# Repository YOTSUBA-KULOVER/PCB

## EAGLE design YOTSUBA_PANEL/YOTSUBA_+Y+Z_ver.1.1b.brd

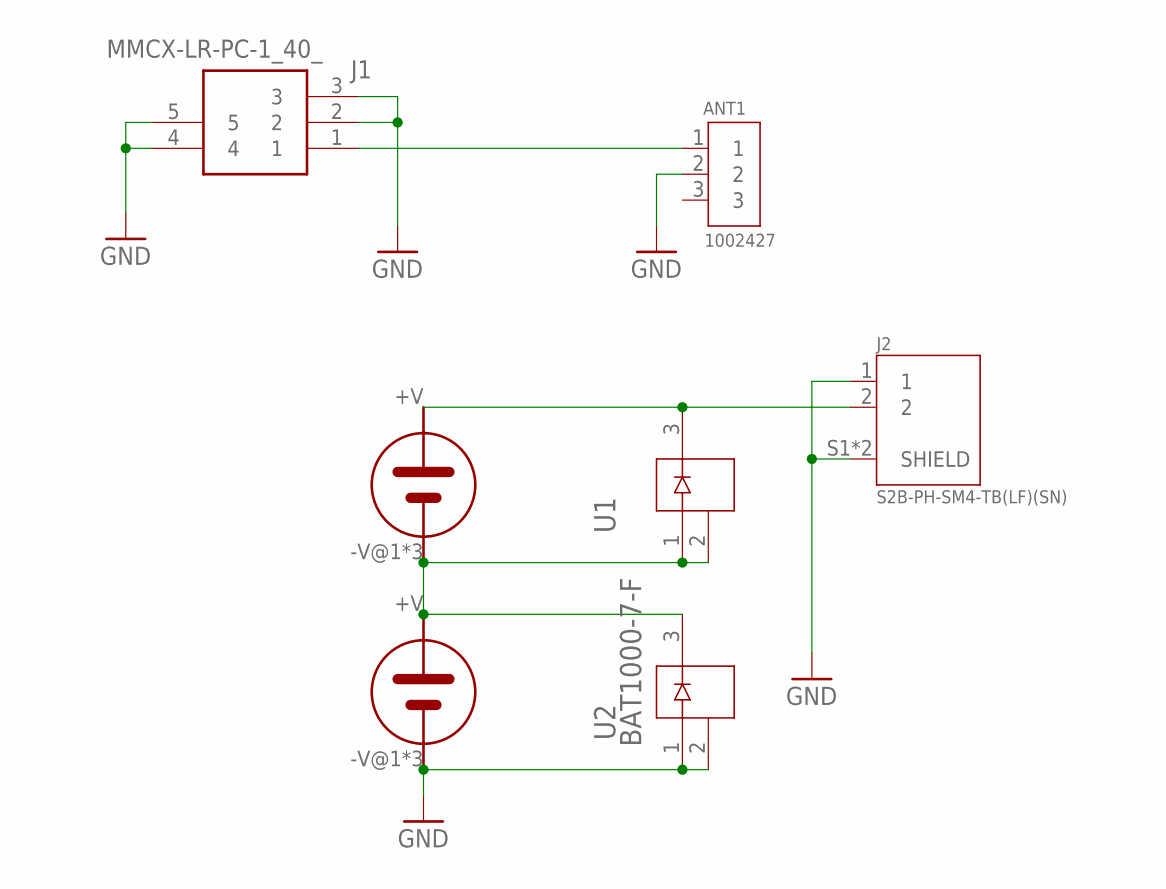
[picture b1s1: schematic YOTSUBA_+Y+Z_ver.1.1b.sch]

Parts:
ANT1: 1002427; ANTENNA_1002427
J1: MMCX-LR-PC-1_40_; MMCXLRPC140
J2: S2B-PH-SM4-TB(LF)(SN); JST_S2B-PH-SM4-TB(LF)(SN)
U1, U2: BAT1000-7-F; SOT23_BAT_DIO
U$2, U$3: 3G30A; SOLAR_3G30A

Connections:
GND: ANT1.2, J1.2, J1.3, J1.4, J1.5, J2.1, J2.S1 (SHIELD), J2.S2 (SHIELD), U2.1, U2.2, U$3.-V@1 (-V), U$3.-V@2 (-V), U$3.-V@3 (-V)
unnamed: U1.1, U1.2, U2.3, U$2.-V@1 (-V), U$2.-V@2 (-V), U$2.-V@3 (-V), U$3.+V
unnamed: J2.2, U1.3, U$2.+V
RF2: ANT1.1, J1.1

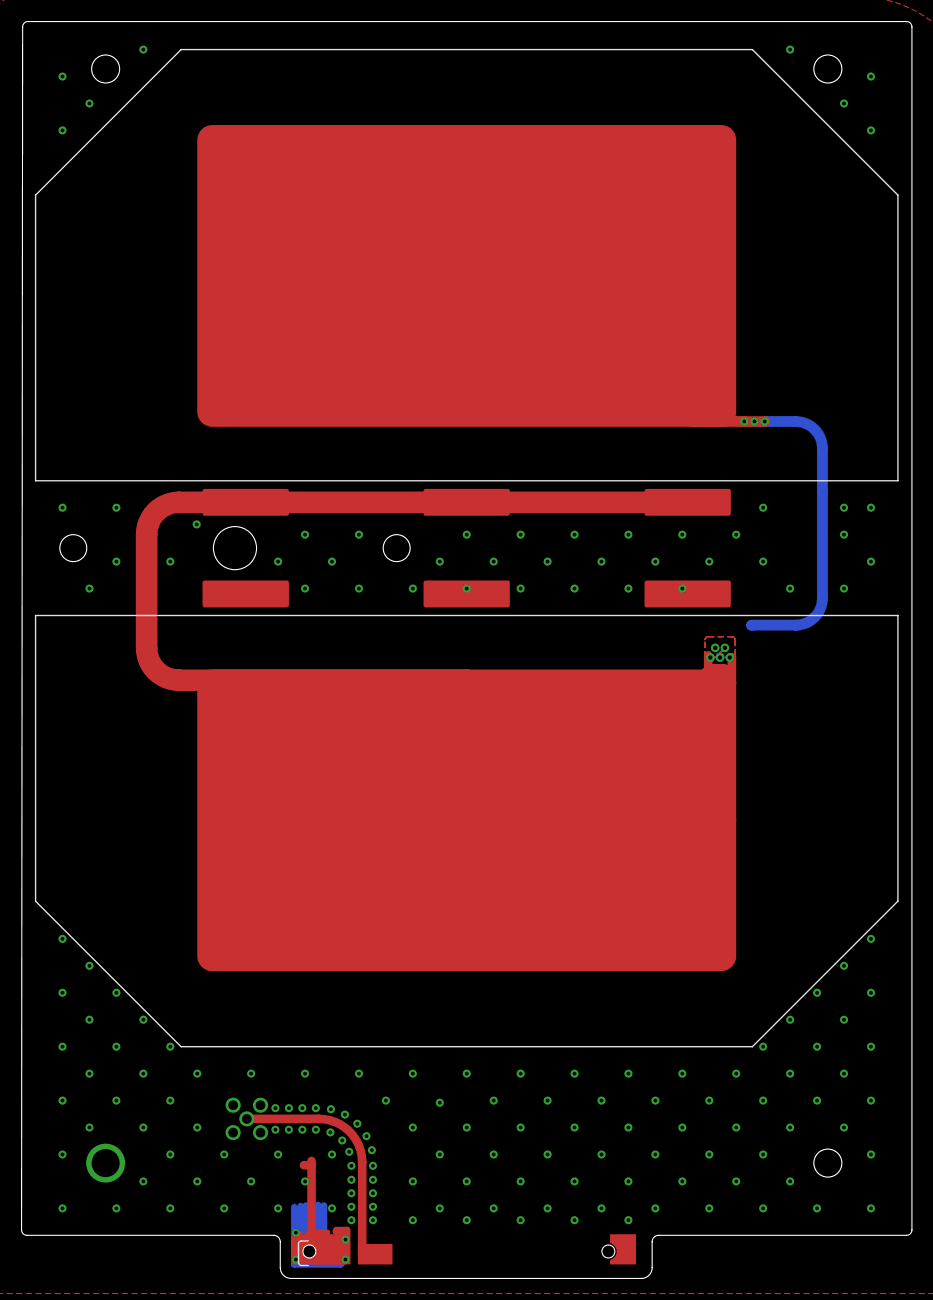
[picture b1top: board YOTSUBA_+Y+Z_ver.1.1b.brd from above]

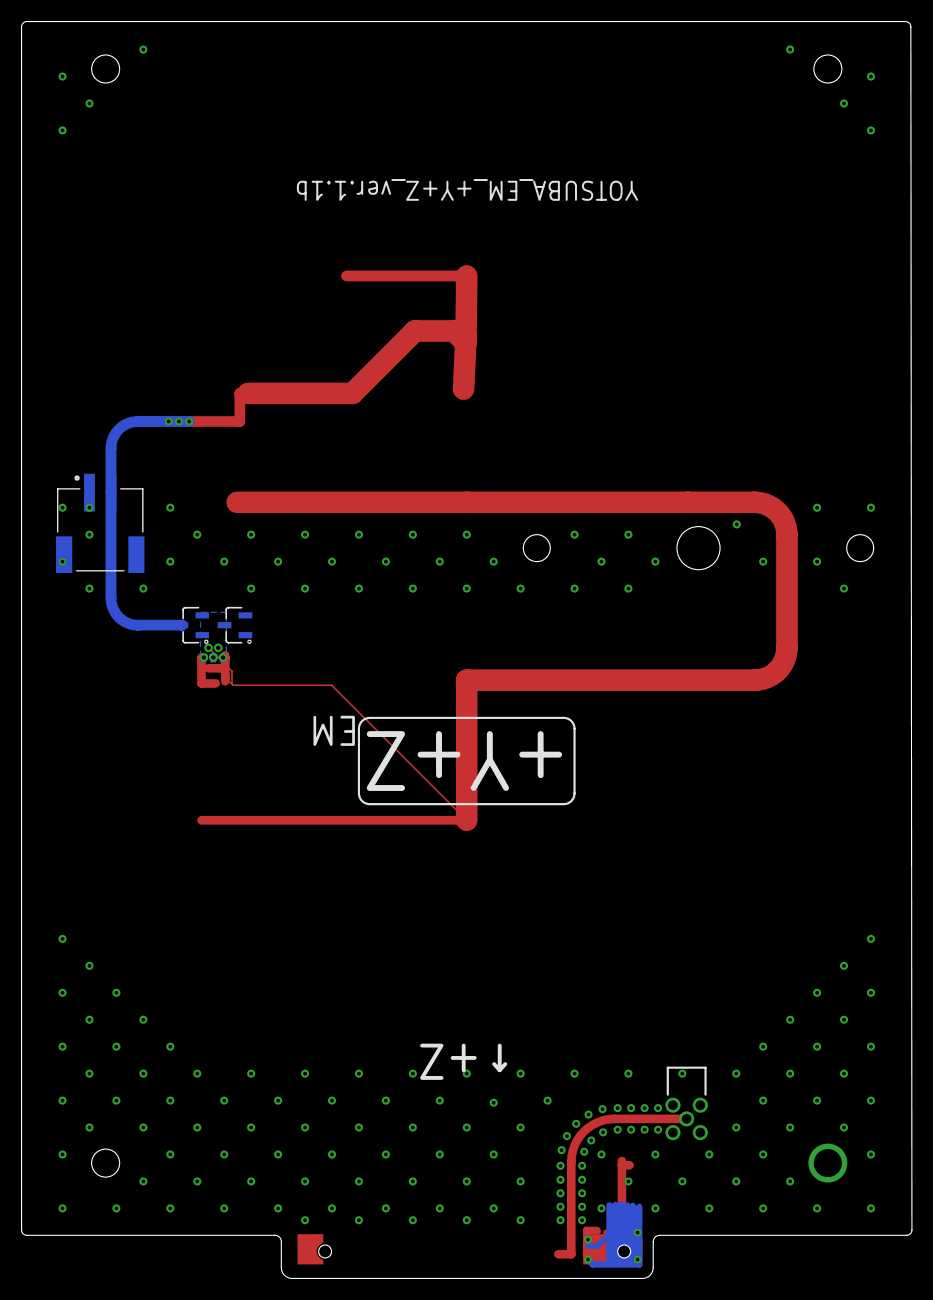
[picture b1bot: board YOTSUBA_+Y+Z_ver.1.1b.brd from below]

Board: 2 copper layers, 82.6 x 116.6 mm, 7 parts (4 on the bottom side), 4 nets.

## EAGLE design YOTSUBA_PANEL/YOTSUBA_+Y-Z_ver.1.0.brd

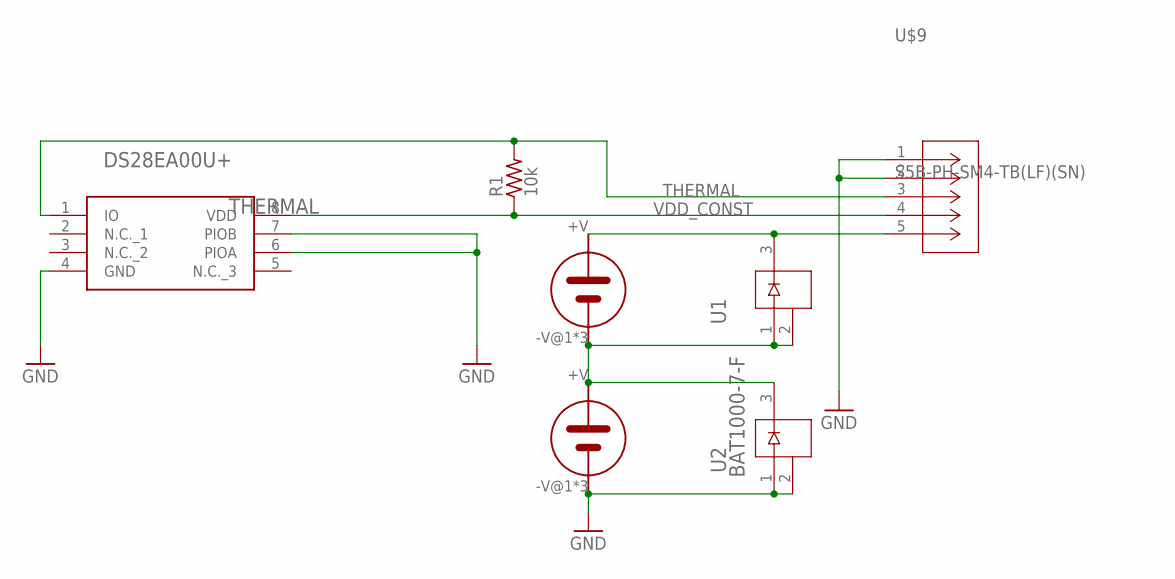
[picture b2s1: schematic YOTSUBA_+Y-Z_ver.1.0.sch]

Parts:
R1: 10k; R0805
THERMAL: DS28EA00U+; SOP65P490X110-8N
U1, U2: BAT1000-7-F; SOT23_BAT_DIO
U$2, U$3: 3G30A; SOLAR_3G30A
U$9: S5B-PH-SM4-TB(LF)(SN); CONN_S5B-PH-SM4-TB_JST

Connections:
GND: THERMAL.4 (GND), THERMAL.6 (PIOA), THERMAL.7 (PIOB), U2.1, U2.2, U$3.-V@1 (-V), U$3.-V@2 (-V), U$3.-V@3 (-V), U$9.1, U$9.2
unnamed: U1.1, U1.2, U2.3, U$2.-V@1 (-V), U$2.-V@2 (-V), U$2.-V@3 (-V), U$3.+V
unnamed: U1.3, U$2.+V, U$9.5
THERMAL: R1.2, THERMAL.1 (IO), U$9.3
VDD_CONST: R1.1, THERMAL.8 (VDD), U$9.4

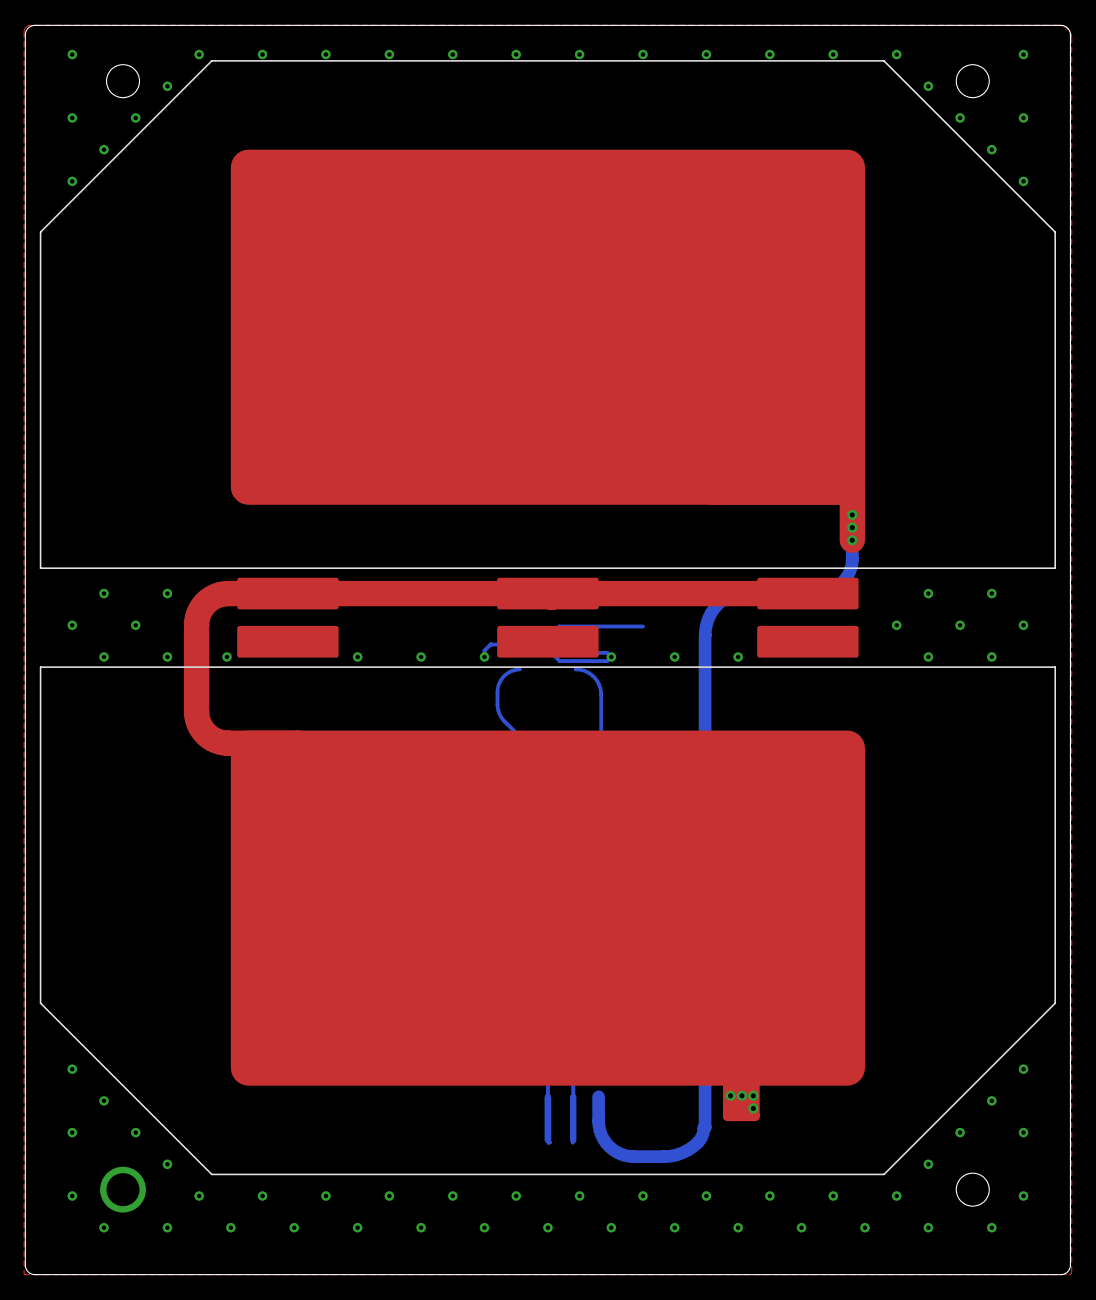
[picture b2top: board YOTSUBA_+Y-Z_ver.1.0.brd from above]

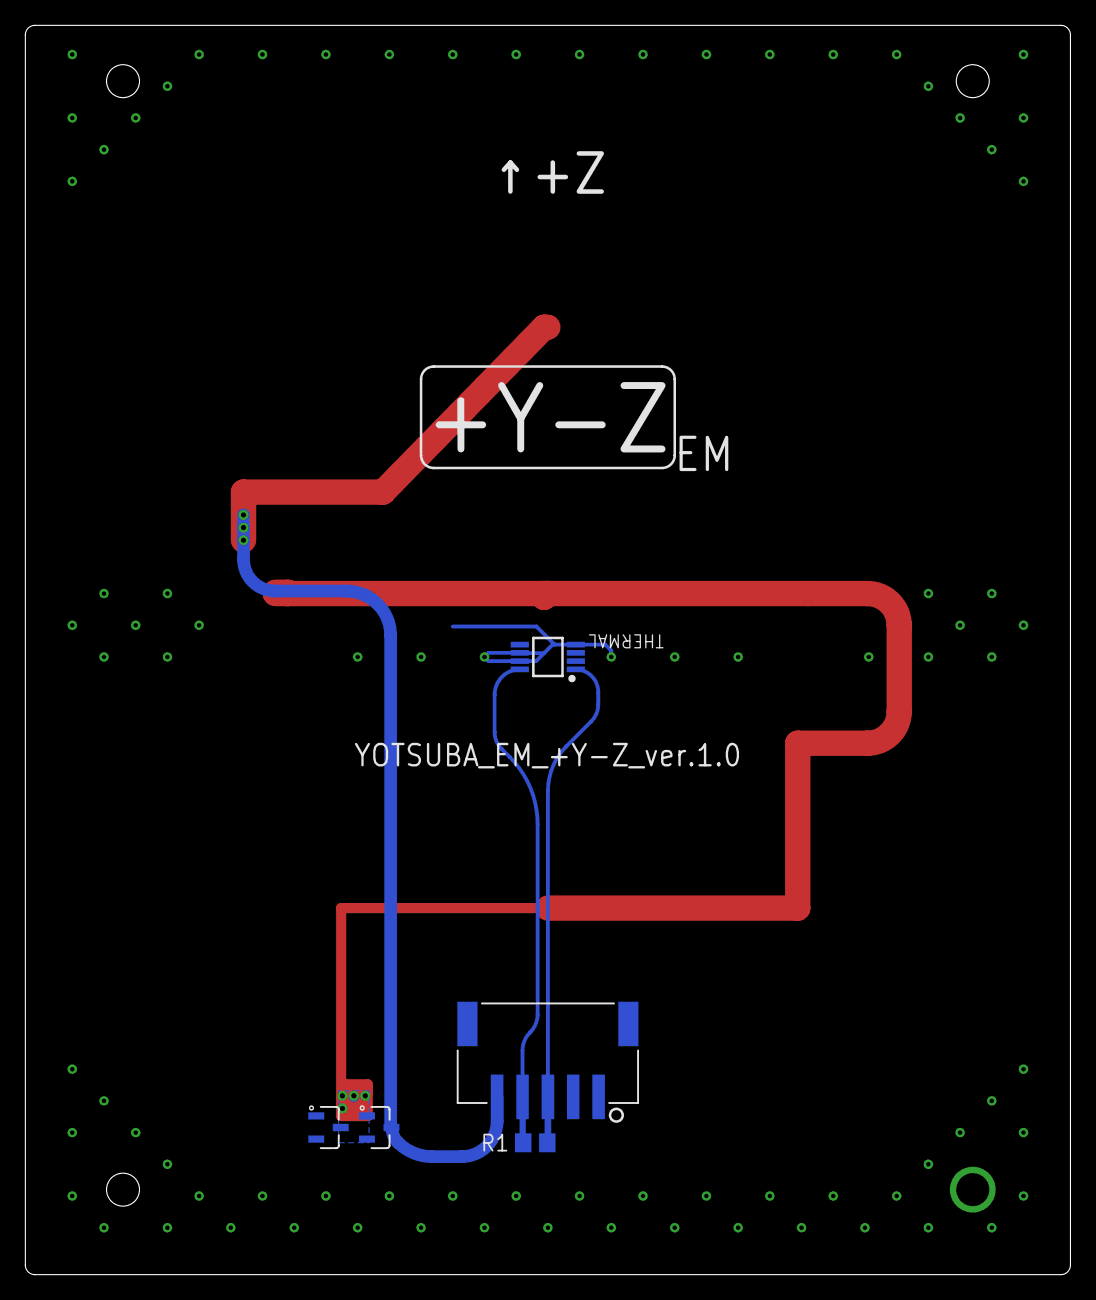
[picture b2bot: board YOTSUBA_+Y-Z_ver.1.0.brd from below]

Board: 2 copper layers, 82.4 x 98.5 mm, 7 parts (5 on the bottom side), 5 nets.

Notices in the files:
parts and their libraries:
COPYRIGHT: Copyright (C) 2023 Ultra Librarian. All rights reserved.
